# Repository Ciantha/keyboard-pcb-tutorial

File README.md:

# keyboard-pcb-tutorial
 time to learn pcb design I guess...

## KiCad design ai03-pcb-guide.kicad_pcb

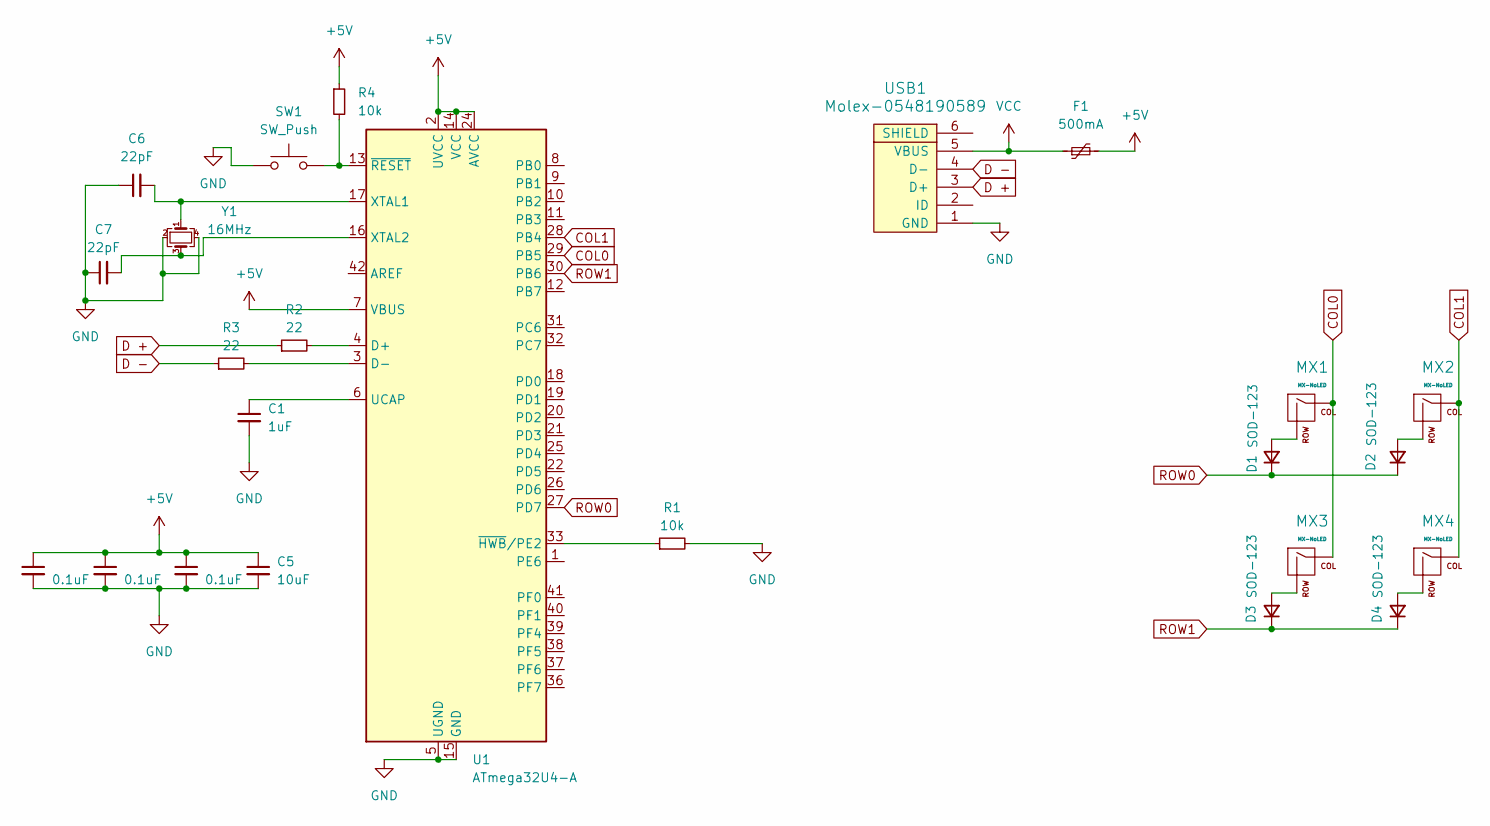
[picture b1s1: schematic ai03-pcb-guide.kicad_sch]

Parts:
C1: 1uF; C_0805_2012Metric_Pad1.18x1.45mm_HandSolder
C2, C3, C4: 0.1uF; C_0805_2012Metric_Pad1.18x1.45mm_HandSolder
C5: 10uF; C_0805_2012Metric_Pad1.18x1.45mm_HandSolder
C6, C7: 22pF; C_0805_2012Metric_Pad1.18x1.45mm_HandSolder
D1, D2, D3, D4: SOD-123; D_SOD-123
F1: 500mA; Fuse_1206_3216Metric
MX1, MX2, MX3, MX4: MX-NoLED; MX-1U-NoLED
R1, R4: 10k; R_0805_2012Metric
R2, R3: 22; R_0805_2012Metric
SW1: SW_Push; SKQG-1155865
U1: ATmega32U4-A; TQFP-44_10x10mm_P0.8mm
USB1: Molex-0548190589
Y1: 16MHz; Crystal_SMD_3225-4Pin_3.2x2.5mm

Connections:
+5V: C2.1, C3.1, C4.1, C5.1, F1.2, R4.1, U1.2 (UVCC), U1.7 (VBUS), U1.14 (VCC), U1.24 (AVCC), U1.34 (VCC), U1.44 (AVCC)
COL0: MX1.1 (COL), MX3.1 (COL), U1.29 (PB5)
COL1: MX2.1 (COL), MX4.1 (COL), U1.28 (PB4)
D +: R2.1, USB1.3 (D+)
D -: R3.1, USB1.4 (D-)
GND: C1.2, C2.2, C3.2, C4.2, C5.2, C6.1, C7.1, R1.2, SW1.1, U1.5 (UGND), U1.15 (GND), U1.23 (GND), U1.35 (GND), U1.43 (GND), USB1.1 (GND), Y1.2, Y1.4
unnamed: D1.2 (A), MX1.2 (ROW)
unnamed: D2.2 (A), MX2.2 (ROW)
unnamed: D3.2 (A), MX3.2 (ROW)
unnamed: D4.2 (A), MX4.2 (ROW)
unnamed: R2.2, U1.4 (D+)
unnamed: R3.2, U1.3 (D-)
unnamed: C1.1, U1.6 (UCAP)
unnamed: C6.2, U1.17 (XTAL1), Y1.1
unnamed: C7.2, U1.16 (XTAL2), Y1.3
unnamed: R1.1, U1.33 (~HWB/PE2)
unnamed: R4.2, SW1.2, U1.13 (~RESET)
ROW0: D1.1 (K), D2.1 (K), U1.27 (PD7)
ROW1: D3.1 (K), D4.1 (K), U1.30 (PB6)
VCC: F1.1, USB1.5 (VBUS)

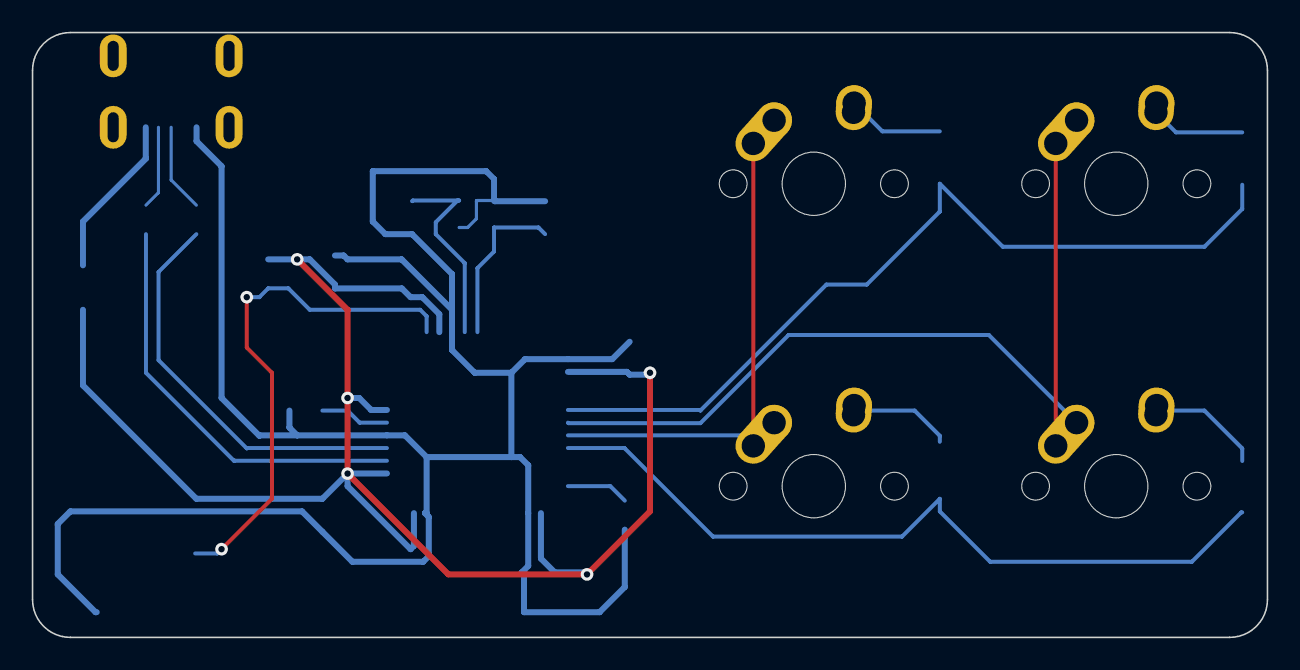
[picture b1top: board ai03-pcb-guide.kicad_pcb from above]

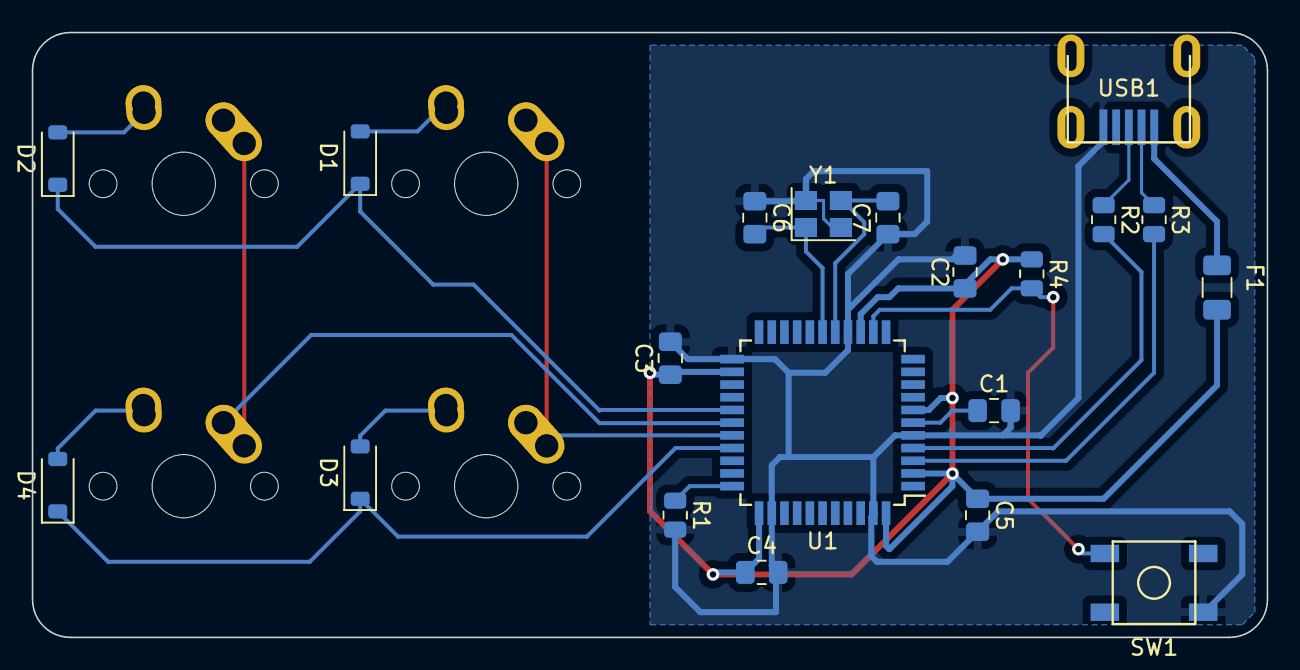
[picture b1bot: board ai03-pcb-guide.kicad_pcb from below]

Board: 2 copper layers, 77.8 x 38.1 mm, 24 parts (20 on the bottom side), 20 nets.

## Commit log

2023-07-07 set up kicad project
2023-07-07 Add submodules
2023-07-07 add footprint libraries
2023-07-07 changed footprints to follow tutorial
2023-07-07 schematic completed
2023-07-07 components placed
2023-07-07 probably routed now
2023-07-07 added matrix to mcu pins
2023-07-07 generated gerber files
2023-07-08 closing project
